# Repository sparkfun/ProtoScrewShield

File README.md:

ProtoScrewShield
========================================

[*ProtoScrewShield (DEV-09729)*](https://www.sparkfun.com/products/9729)

The ScrewShield extends all pins of the Arduino out to 3.5mm pitch screw terminals. 
It also has a lot of the utility provided by Arduino Protoshield, including: a large prototyping space of both connected and unconnected 0.1" spaced through-holes, a couple 5V and GND busses, a reset button, general use push button, and a 5mm yellow LED.

Repository Contents
-------------------

* **/Hardware** - Eagle design files (.brd, .sch)
* **/Production** - Production panel files (.brd)

Documentation
--------------
* **[SparkFun Fritzing repo](https://github.com/sparkfun/Fritzing_Parts)** - Fritzing diagrams for SparkFun products.
* **[SparkFun 3D Model repo](https://github.com/sparkfun/3D_Models)** - 3D models of SparkFun products. 

License Information
-------------------
This product is _**open source**_! 

The **hardware** is released under [Creative Commons ShareAlike 4.0 International](https://creativecommons.org/licenses/by-sa/4.0/).

Please use, reuse, and modify these files as you see fit. Please maintain attribution to SparkFun Electronics and release anything derivative under the same license.

Distributed as-is; no warranty is given.

- Your friends at SparkFun.

_**Note:**  This product is a collaboration with Tod Kurt, John Edgar Park, and Brian Jepson of WingShield Industries and a portion of each sale goes to them for product support and continued development._

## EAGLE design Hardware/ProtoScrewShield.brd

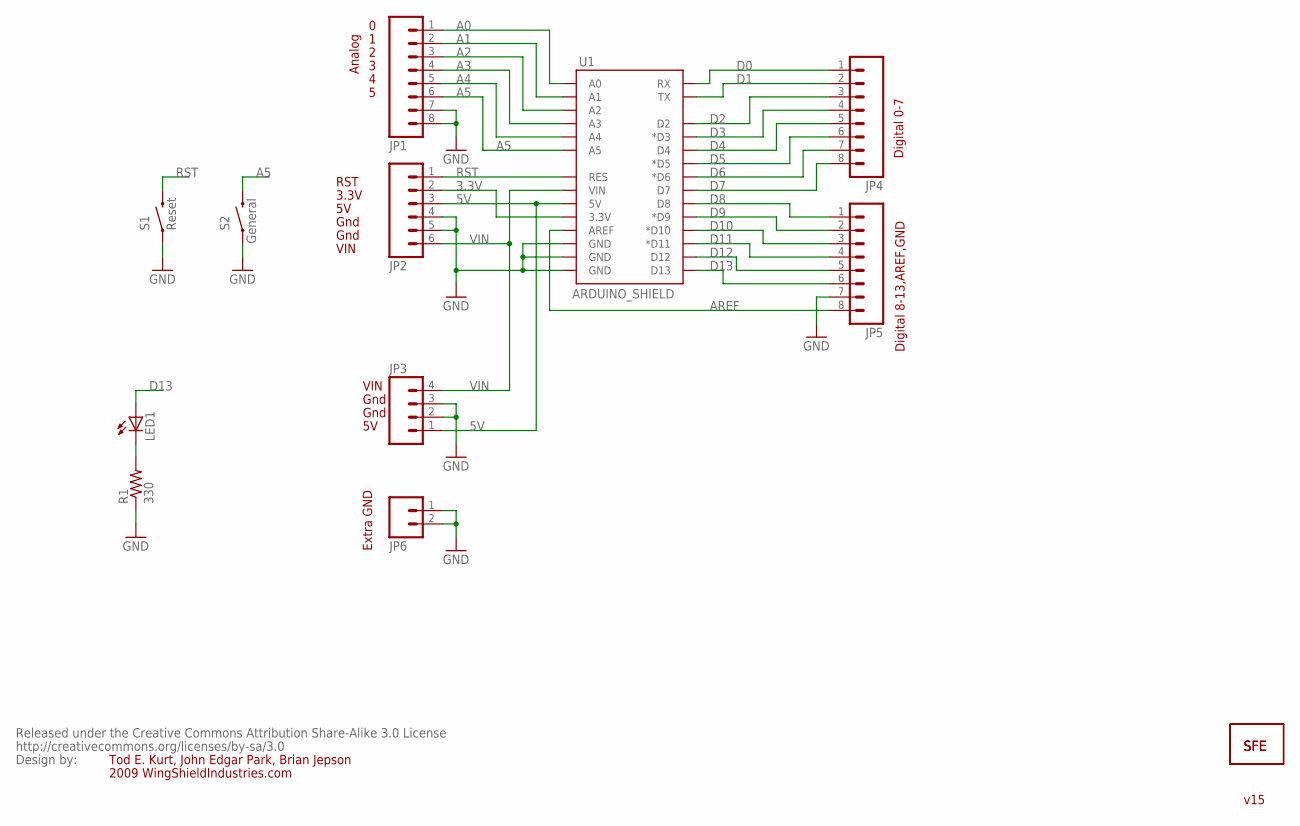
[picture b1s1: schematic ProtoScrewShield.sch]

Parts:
JP1, JP4, JP5: M083.5MM-8; SCREWTERMINAL-3.5MM-8
JP2: M063.5MM-6; SCREWTERMINAL-3.5MM-6
JP3: M04SCREW; SCREWTERMINAL-3.5MM-4
JP6: M023.5MM; SCREWTERMINAL-3.5MM-2
JP7: LOGO-SFENEW; SFE-NEW-WEBLOGO
JP8: LOGO-SFESK; SFE-LOGO-FLAME
LED1: LED5MM
R1: 330; AXIAL-0.3
S1: Reset; TACTILE-PTH
S2: General; TACTILE-PTH
U1: ARDUINO_SHIELD; DUEMILANOVE_SHIELD_NOHOLES
U$1: CREATIVE_COMMONS

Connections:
3.3V: JP2.2, U1.3.3V
5V: JP2.3, JP3.1, U1.5V
A0: JP1.1, U1.A0
A1: JP1.2, U1.A1
A2: JP1.3, U1.A2
A3: JP1.4, U1.A3
A4: JP1.5, U1.A4
A5: JP1.6, S2.3 (2), U1.A5
AREF: JP5.8, U1.AREF
D0: JP4.1, U1.RX
D1: JP4.2, U1.TX
D2: JP4.3, U1.D2
D3: JP4.4, U1.D3 (*D3)
D4: JP4.5, U1.D4
D5: JP4.6, U1.D5 (*D5)
D6: JP4.7, U1.D6 (*D6)
D7: JP4.8, U1.D7
D8: JP5.1, U1.D8
D9: JP5.2, U1.D9 (*D9)
D10: JP5.3, U1.D10 (*D10)
D11: JP5.4, U1.D11 (*D11)
D12: JP5.5, U1.D12
D13: JP5.6, LED1.A, U1.D13
GND: JP1.7, JP1.8, JP2.4, JP2.5, JP3.2, JP3.3, JP5.7, JP6.1, JP6.2, R1.P$1 (1), S1.1, S2.1, U1.GND@0 (GND), U1.GND@1 (GND), U1.GND@2 (GND)
unnamed: LED1.K (C), R1.P$2 (2)
RST: JP2.1, S1.3 (2), U1.RES
VIN: JP2.6, JP3.4, U1.VIN

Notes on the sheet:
Analog
Gnd
VIN
3.3V
RST
2009 WingShieldIndustries.com
Tod E. Kurt, John Edgar Park, Brian Jepson
Digital 8-13,AREF,GND
Digital 0-7
Extra GND
v15

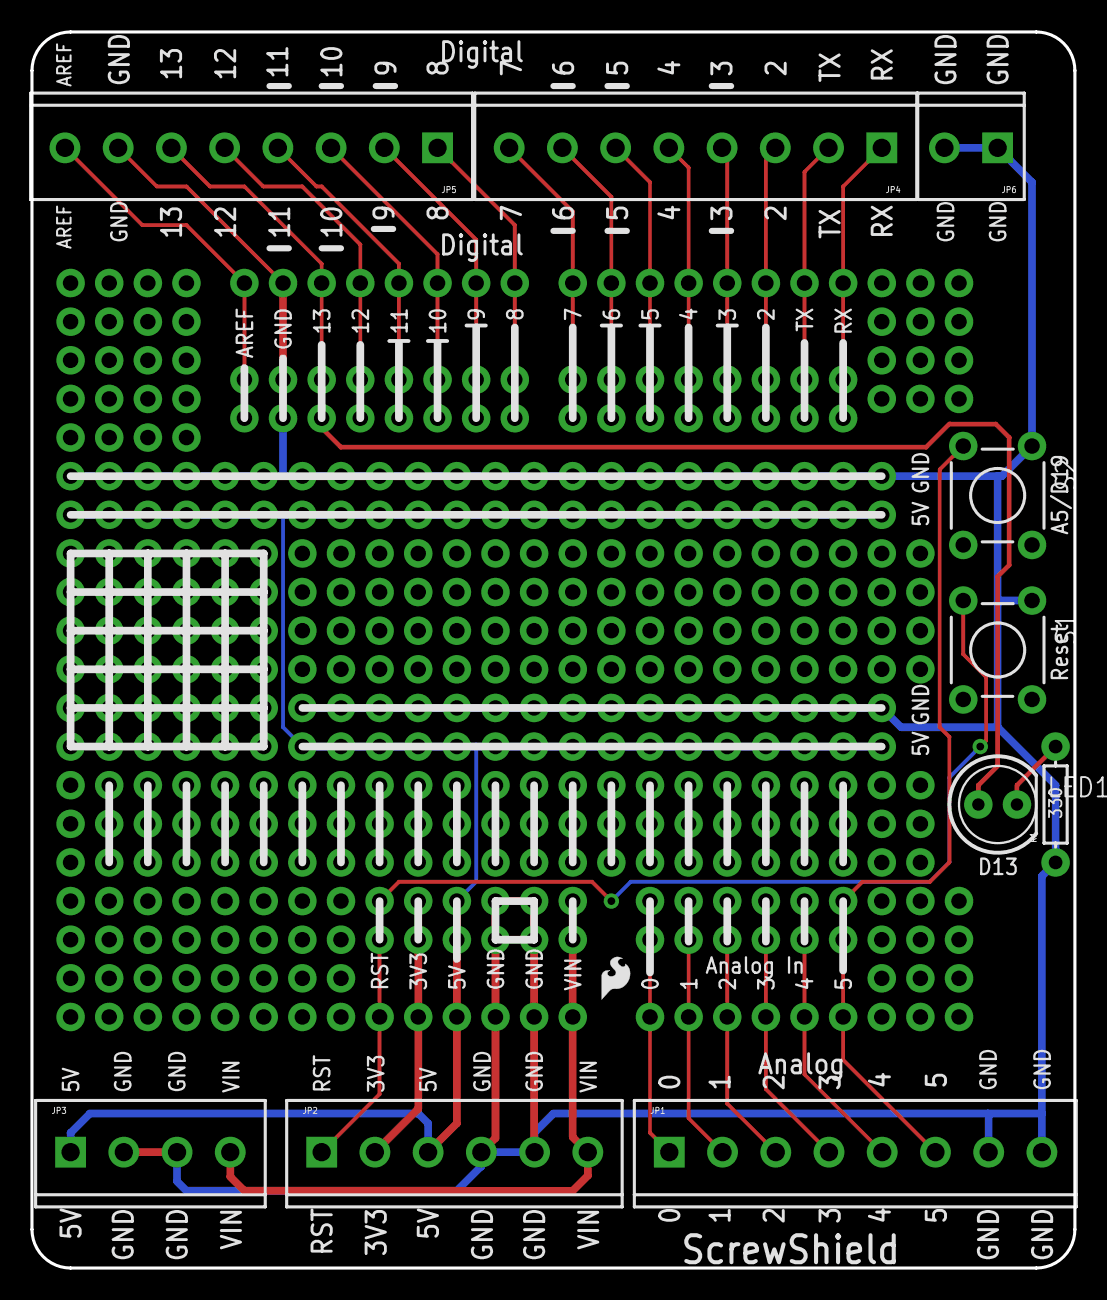
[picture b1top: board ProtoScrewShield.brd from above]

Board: 2 copper layers, 68.6 x 81.3 mm, 14 parts (1 on the bottom side), 27 nets.

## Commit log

2015-05-05 Adding hardware files, updating README

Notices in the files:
parts and their libraries:
SparkFun: Released under the Creative Commons Attribution Share-Alike 3.0 License
SparkFun: http://creativecommons.org/licenses/by-sa/3.0
